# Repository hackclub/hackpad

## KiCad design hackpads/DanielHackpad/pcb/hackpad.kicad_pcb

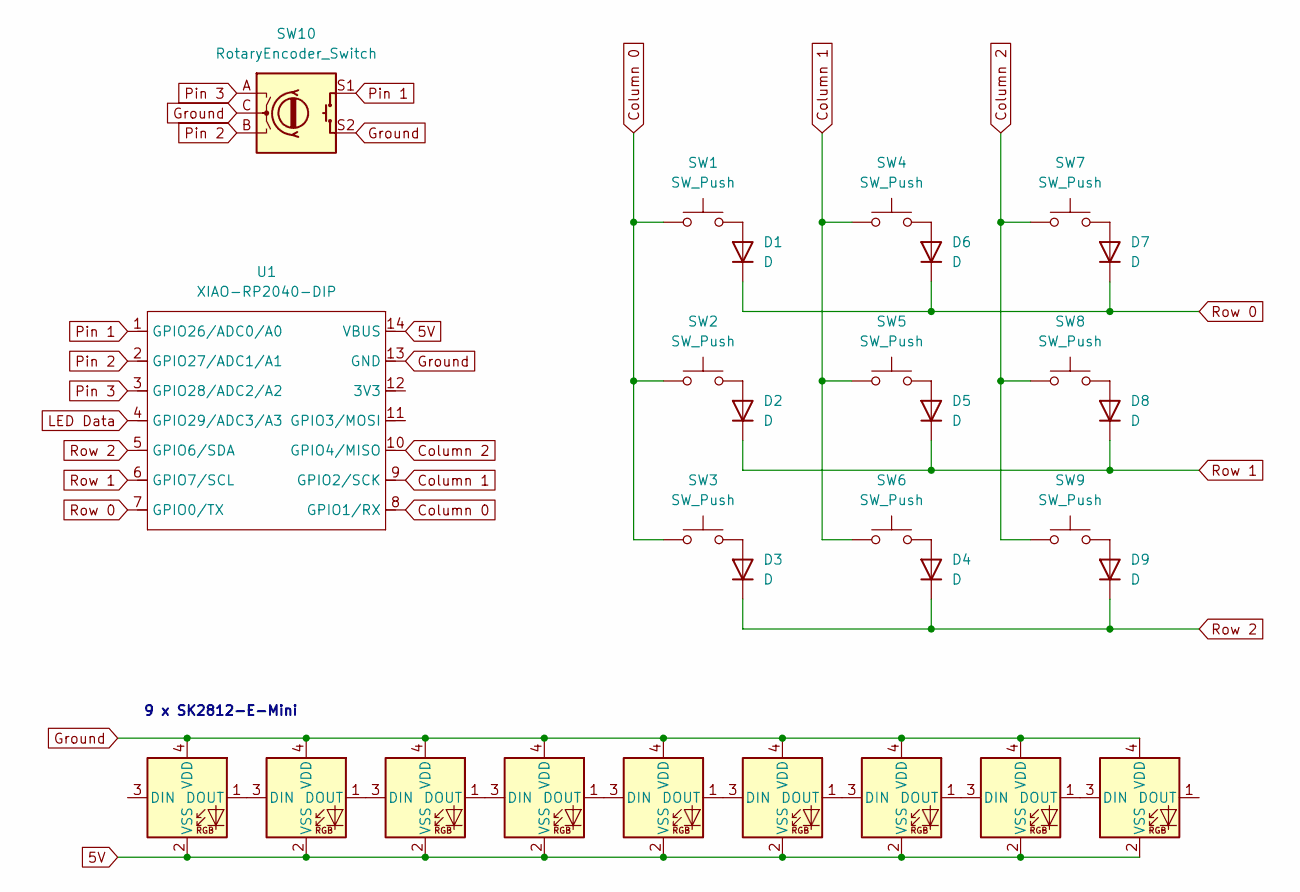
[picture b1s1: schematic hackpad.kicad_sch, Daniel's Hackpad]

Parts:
D1, D2, D3, D4, D5, D6, D7, D8, D9: D; D_DO-35_SOD27_P7.62mm_Horizontal
D10, D11, D12, D13, D14, D15, D16, D17, D19: SK6812MINI; SK6812MINI-E
SW1, SW2, SW3, SW4, SW5, SW6, SW7, SW8, SW9: SW_Push; SW_Cherry_MX_1.00u_PCB
SW10: RotaryEncoder_Switch; RotaryEncoder_Alps_EC11E-Switch_Vertical_H20mm_CircularMoun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
U1: XIAO-RP2040-DIP

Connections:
5V: D10.2 (VSS), D11.2 (VSS), D12.2 (VSS), D13.2 (VSS), D14.2 (VSS), D15.2 (VSS), D16.2 (VSS), D17.2 (VSS), D19.2 (VSS), U1.14 (VBUS)
Column 0: SW1.1, SW2.1, SW3.1, U1.8 (GPIO1/RX)
Column 1: SW4.1, SW5.1, SW6.1, U1.9 (GPIO2/SCK)
Column 2: SW7.1, SW8.1, SW9.1, U1.10 (GPIO4/MISO)
Ground: D10.4 (VDD), D11.4 (VDD), D12.4 (VDD), D13.4 (VDD), D14.4 (VDD), D15.4 (VDD), D16.4 (VDD), D17.4 (VDD), D19.4 (VDD), SW10.C, SW10.S2, U1.13 (GND)
LED Data: U1.4 (GPIO29/ADC3/A3)
unnamed: D1.2 (A), SW1.2
unnamed: D2.2 (A), SW2.2
unnamed: D3.2 (A), SW3.2
unnamed: D4.2 (A), SW6.2
unnamed: D5.2 (A), SW5.2
unnamed: D6.2 (A), SW4.2
unnamed: D7.2 (A), SW7.2
unnamed: D8.2 (A), SW8.2
unnamed: D9.2 (A), SW9.2
unnamed: D10.3 (DIN), D19.1 (DOUT)
unnamed: D10.1 (DOUT), D11.3 (DIN)
unnamed: D11.1 (DOUT), D12.3 (DIN)
unnamed: D12.1 (DOUT), D13.3 (DIN)
unnamed: D13.1 (DOUT), D14.3 (DIN)
unnamed: D14.1 (DOUT), D15.3 (DIN)
unnamed: D15.1 (DOUT), D16.3 (DIN)
unnamed: D16.1 (DOUT), D17.3 (DIN)
Pin 1: SW10.S1, U1.1 (GPIO26/ADC0/A0)
Pin 2: SW10.B, U1.2 (GPIO27/ADC1/A1)
Pin 3: SW10.A, U1.3 (GPIO28/ADC2/A2)
Row 0: D1.1 (K), D6.1 (K), D7.1 (K), U1.7 (GPIO0/TX)
Row 1: D2.1 (K), D5.1 (K), D8.1 (K), U1.6 (GPIO7/SCL)
Row 2: D3.1 (K), D4.1 (K), D9.1 (K), U1.5 (GPIO6/SDA)

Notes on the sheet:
9 x SK2812-E-Mini

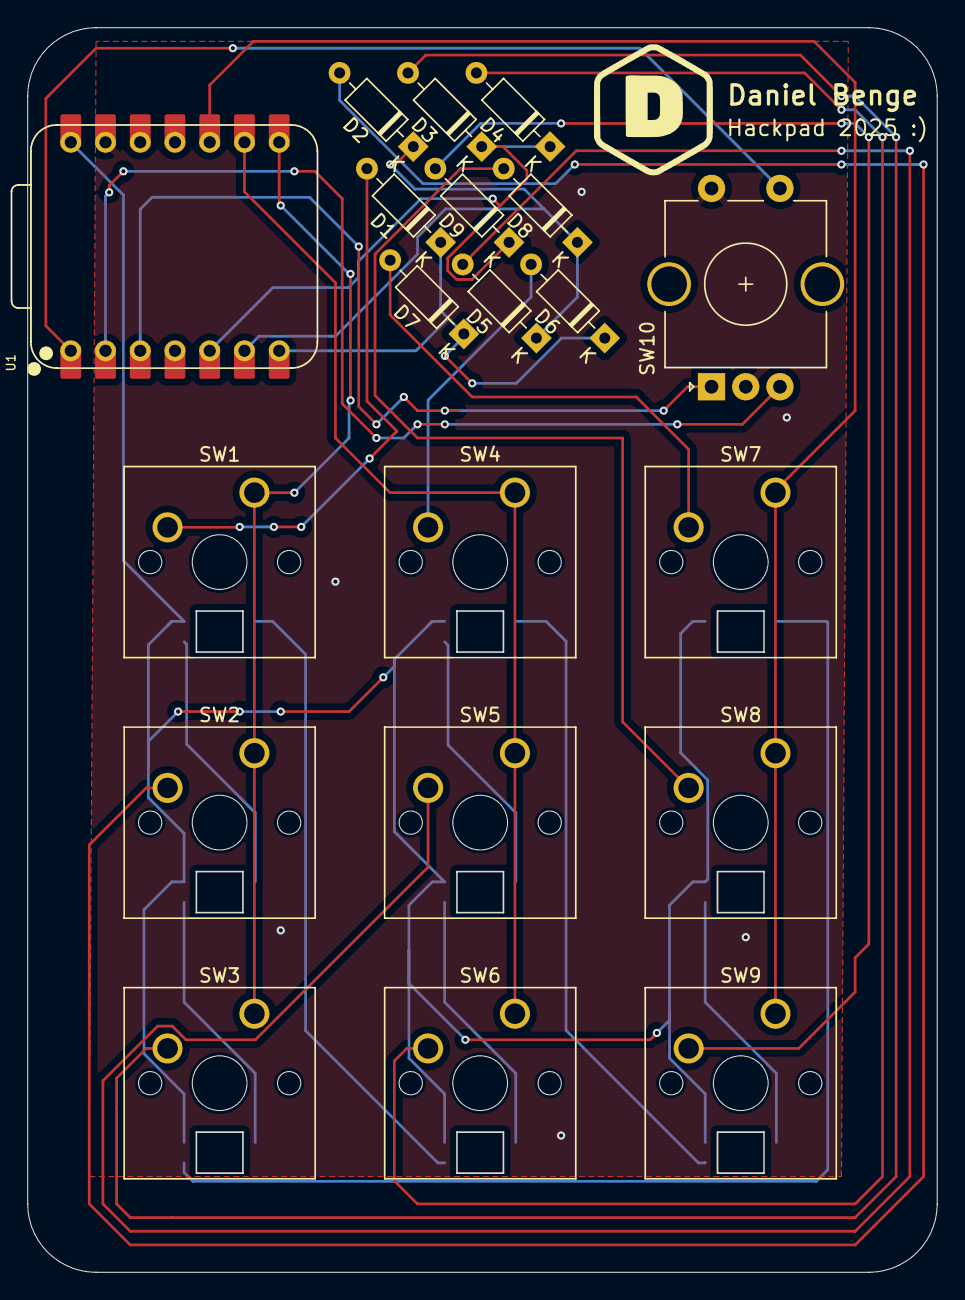
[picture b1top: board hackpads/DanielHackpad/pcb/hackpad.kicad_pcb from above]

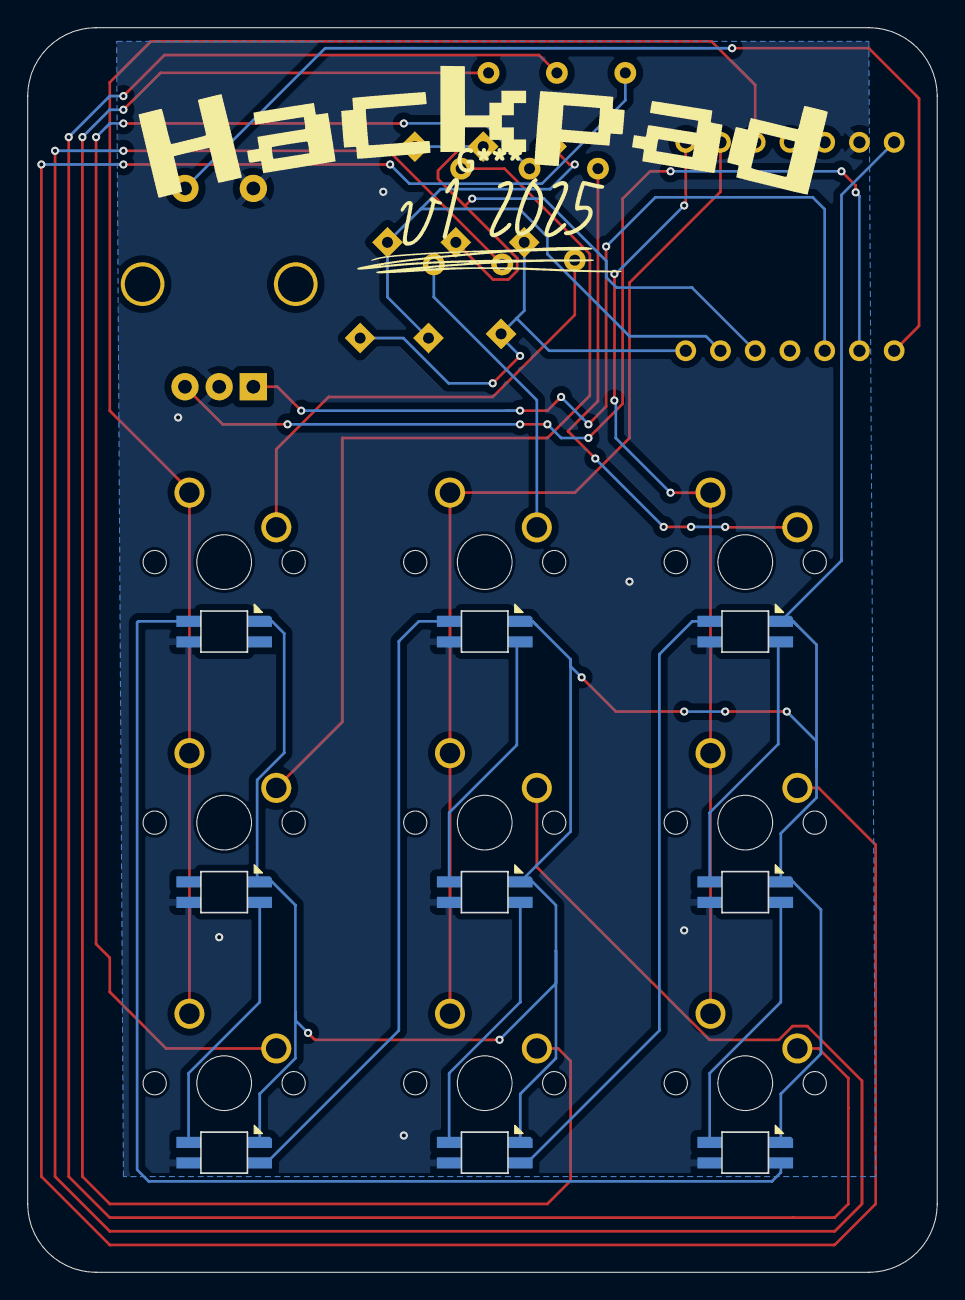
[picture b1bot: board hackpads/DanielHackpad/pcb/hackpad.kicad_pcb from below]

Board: 2 copper layers, 66.5 x 91.0 mm, 29 parts (9 on the bottom side), 28 nets.

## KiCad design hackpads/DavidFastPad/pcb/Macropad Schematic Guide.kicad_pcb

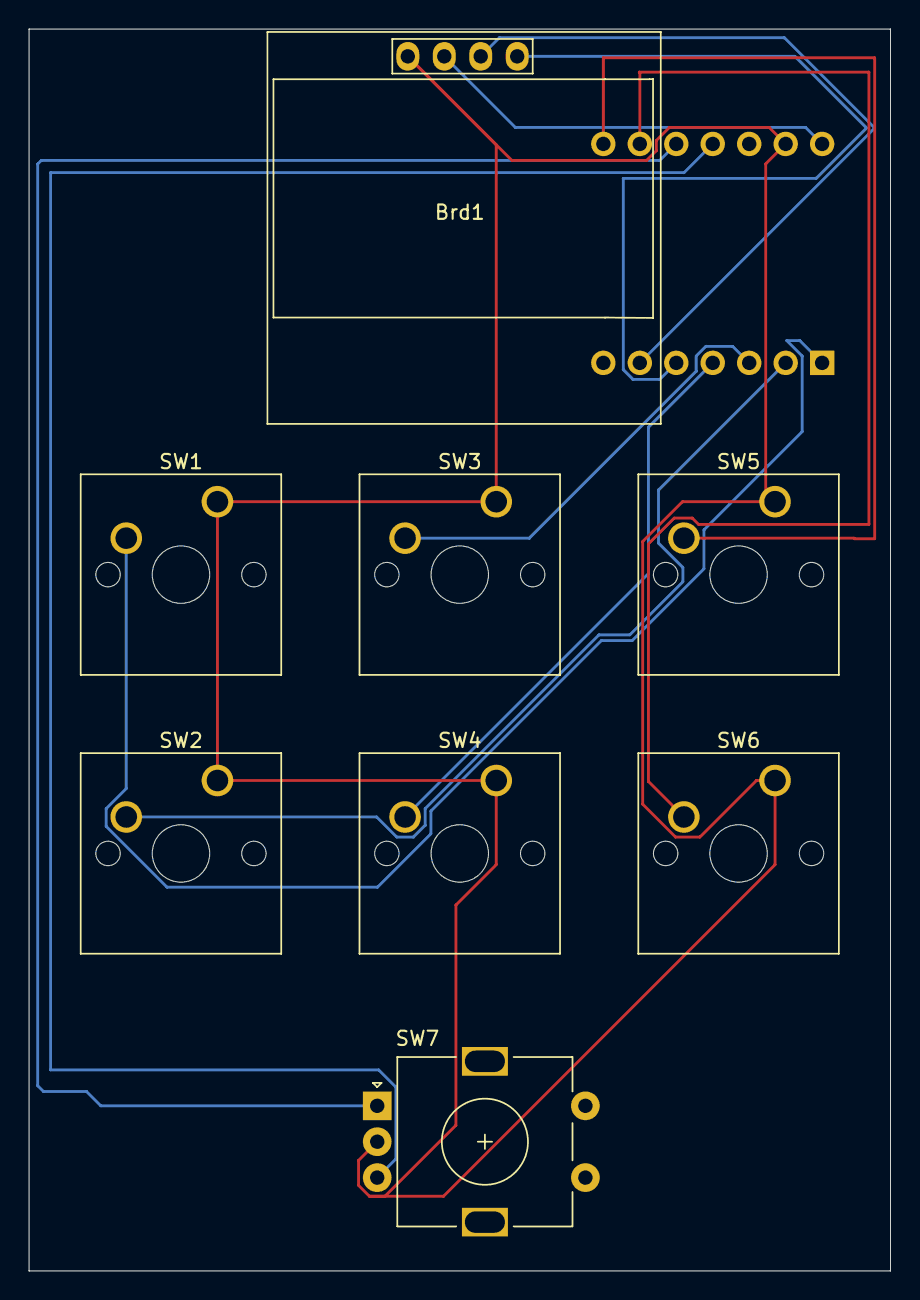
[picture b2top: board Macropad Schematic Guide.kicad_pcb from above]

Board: 2 copper layers, 60.0 x 86.5 mm, 9 parts (1 on the bottom side), 12 nets.

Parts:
Brd1: SSD1306; 128x64OLED
SW1, SW2, SW3, SW4, SW5, SW6: SW_Push; SW_Cherry_MX_1.00u_PCB
SW7: RotaryEncoder; RotaryEncoder_Alps_EC11E-Switch_Vertical_H20mm
U1: Seeed Studio XIAO SAMD21; XIAO-Generic-Thruhole-14P-2.54-21X17.8MM

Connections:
1: SW1.2, U1.1 (PA02_A0_D0)
2: SW2.2, U1.2 (PA4_A1_D1)
3: SW3.2, U1.3 (PA10_A2_D2)
4: SW4.2, U1.4 (PA11_A3_D3)
5: SW5.2, U1.8 (PB09_A7_D7_RX)
6: SW6.2, U1.9 (PA7_A8_D8_SCK)
A: SW7.A, U1.10 (PA5_A9_D9_MISO)
B: SW7.B, U1.11 (PA6_A10_D10_MOSI)
GND: Brd1.1 (GND), SW1.1, SW2.1, SW3.1, SW4.1, SW5.1, SW6.1, SW7.C, U1.13 (GND)
SCL: Brd1.3 (SCL), U1.6 (PA9_A5_D5_SCL)
SDA: Brd1.4 (SDA), U1.5 (PA8_A4_D4_SDA)
VCC: Brd1.2 (VCC), U1.14 (5V)

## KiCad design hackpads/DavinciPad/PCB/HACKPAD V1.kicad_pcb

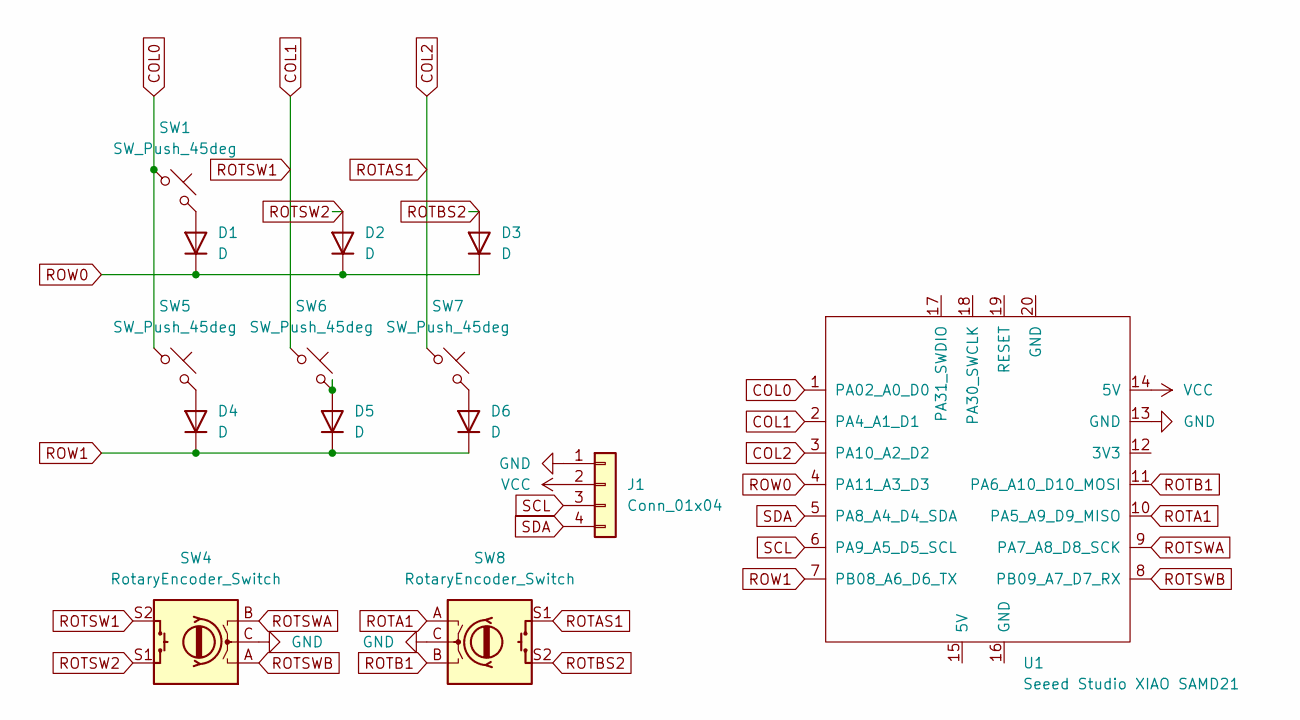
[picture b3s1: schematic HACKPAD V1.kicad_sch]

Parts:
D1, D2, D3, D4, D5, D6: D; D_DO-35_SOD27_P7.62mm_Horizontal
J1: Conn_01x04; SSD1306-0.91-OLED-4pin-128x32
SW1, SW5, SW6, SW7: SW_Push_45deg; SW_Cherry_MX_1.00u_PCB
SW4, SW8: RotaryEncoder_Switch; RotaryEncoder_Alps_EC11E-Switch_Vertical_H20mm
U1: Seeed Studio XIAO SAMD21; XIAO-Generic-Thruhole-14P-2.54-21X17.8MM

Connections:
COL0: SW1.1, SW5.1, U1.1 (PA02_A0_D0)
COL1: SW4.S2, SW6.1, U1.2 (PA4_A1_D1)
COL2: SW7.1, SW8.S1, U1.3 (PA10_A2_D2)
GND: J1.1, SW4.C, SW8.C, U1.13 (GND)
unnamed: D1.2 (A), SW1.2
unnamed: D4.2 (A), SW5.2
unnamed: D5.2 (A), SW6.2
unnamed: D6.2 (A), SW7.2
ROTA1: SW8.A, U1.10 (PA5_A9_D9_MISO)
ROTB1: SW8.B, U1.11 (PA6_A10_D10_MOSI)
ROTBS2: D3.2 (A), SW8.S2
ROTSW2: D2.2 (A), SW4.S1
ROTSWA: SW4.B, U1.9 (PA7_A8_D8_SCK)
ROTSWB: SW4.A, U1.8 (PB09_A7_D7_RX)
ROW0: D1.1 (K), D2.1 (K), D3.1 (K), U1.4 (PA11_A3_D3)
ROW1: D4.1 (K), D5.1 (K), D6.1 (K), U1.7 (PB08_A6_D6_TX)
SCL: J1.3, U1.6 (PA9_A5_D5_SCL)
SDA: J1.4, U1.5 (PA8_A4_D4_SDA)
VCC: J1.2, U1.14 (5V)

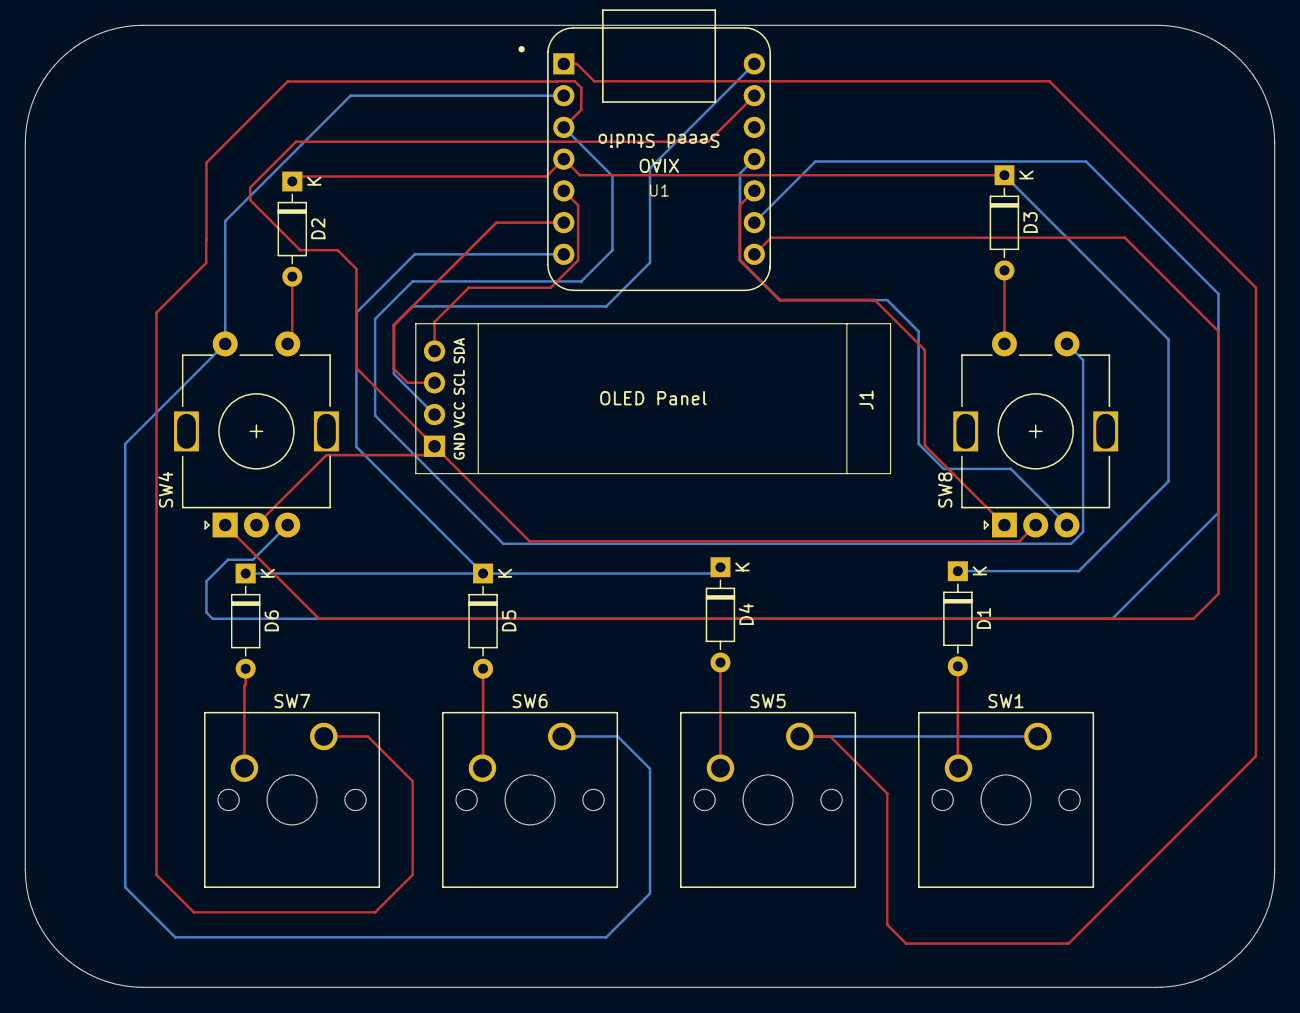
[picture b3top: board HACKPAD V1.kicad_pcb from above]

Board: 2 copper layers, 100.0 x 77.0 mm, 14 parts (0 on the bottom side), 19 nets.

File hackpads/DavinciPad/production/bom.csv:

Designator,Footprint,Quantity,Value,LCSC Part #
"D1, D2, D3, D4, D5, D6",D_DO-35_SOD27_P7.62mm_Horizontal,6,D,
J1,SSD1306-0.91-OLED-4pin-128x32,1,Conn_01x04,
"SW1, SW5, SW6, SW7",SW_Cherry_MX_1.00u_PCB,4,SW_Push_45deg,
"SW4, SW8",RotaryEncoder_Alps_EC11E-Switch_Vertical_H20mm,2,RotaryEncoder_Switch,
U1,XIAO-Generic-Thruhole-14P-2.54-21X17.8MM,1,Seeed Studio XIAO SAMD21,

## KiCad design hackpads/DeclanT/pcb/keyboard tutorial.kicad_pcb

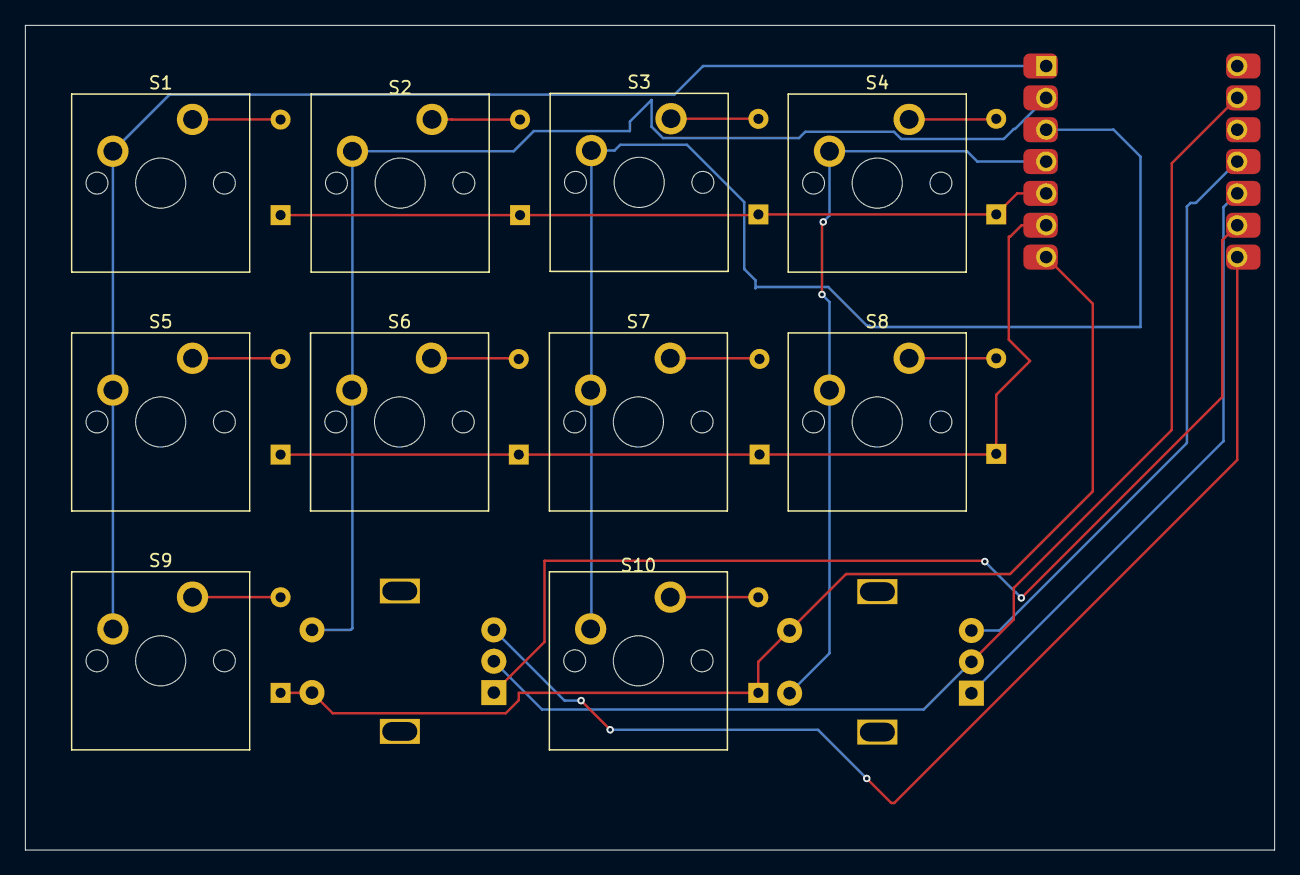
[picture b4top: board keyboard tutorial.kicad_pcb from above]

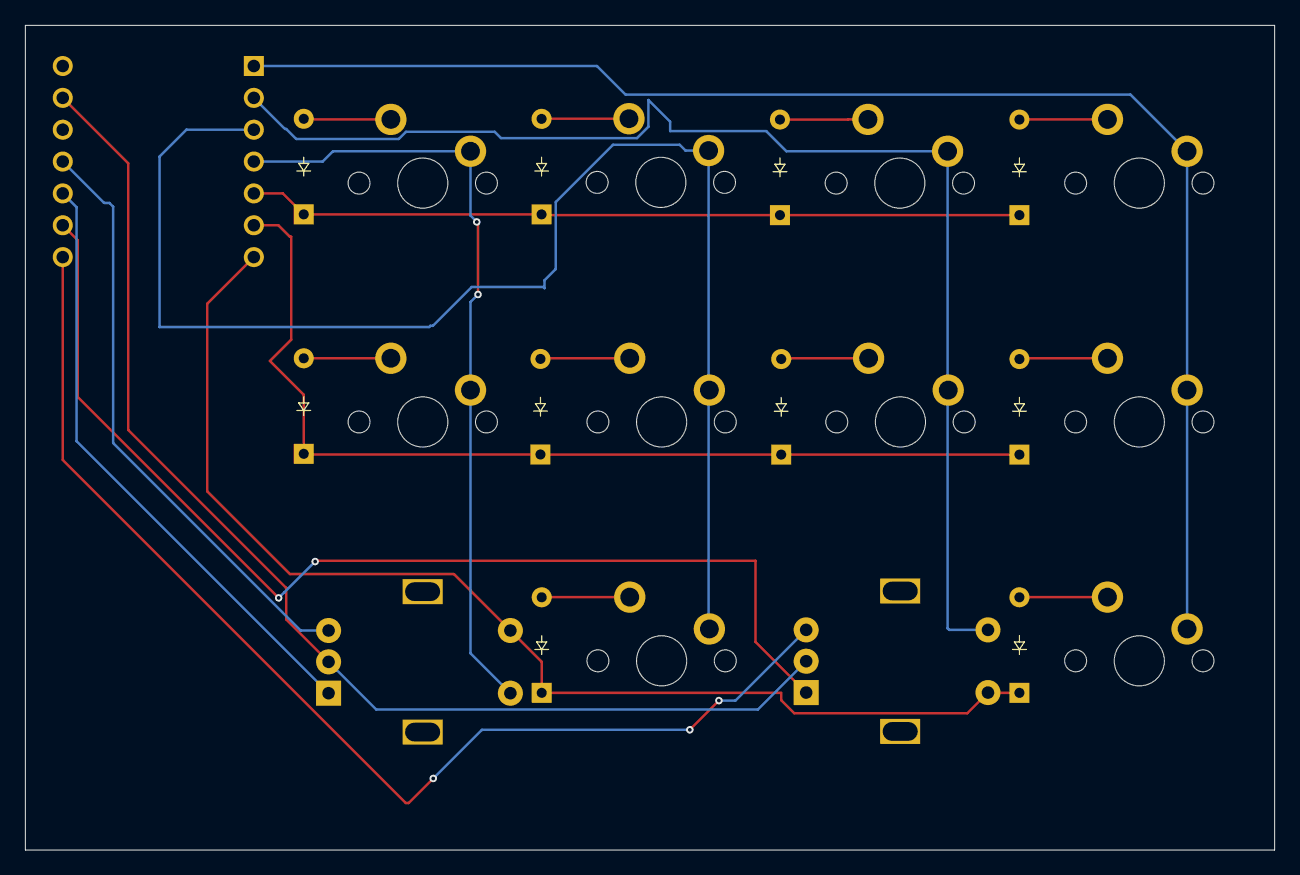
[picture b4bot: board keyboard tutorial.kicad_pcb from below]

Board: 2 copper layers, 99.6 x 65.8 mm, 23 parts (10 on the bottom side), 22 nets.

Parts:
D1, D2, D3, D4, D5, D6, D7, D9, D10, D11: Diode; Diode_DO-35
S1, S2, S3, S4, S5, S6, S7, S8, S9, S10: Keyswitch; MX_PCB_1.00u
SW1, SW2: RotaryEncoder_Switch; Encoder_EC11_MX
U2: MOUDLE-SEEEDUINO-XIAO; Seeed_XIAO_RP2040

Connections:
GND: SW1.C, SW2.C, U2.13 (GND)
unnamed: D1.2 (A), S1.2
unnamed: D2.2 (A), S3.2
unnamed: D3.2 (A), S2.2
unnamed: D4.2 (A), S5.2
unnamed: D5.2 (A), S6.2
unnamed: D6.2 (A), S7.2
unnamed: D7.2 (A), S9.2
unnamed: D9.2 (A), S10.2
unnamed: D10.2 (A), S4.2
unnamed: D11.2 (A), S8.2
Rotary 1: SW1.B, U2.11 (PA6_A10_D10_MOSI)
Rotary 2: SW1.A, U2.10 (PA5_A9_D9_MISO)
Rotary 3: SW2.A, U2.9 (PA7_A8_D8_SCK)
Rotary 4: SW2.B, U2.8 (PB09_A7_D7_RX)
column 0: S1.1, S5.1, S9.1, U2.1 (PA02_A0_D0)
column 1: S2.1, S6.1, SW2.S1, U2.2 (PA4_A1_D1)
column 2: S3.1, S7.1, S10.1, U2.3 (PA10_A2_D2)
column 3: S4.1, S8.1, SW1.S2, U2.4 (PA11_A3_D3)
row 0: D1.1 (K), D2.1 (K), D3.1 (K), D10.1 (K), U2.5 (PA8_A4_D4_SDA)
row 1: D4.1 (K), D5.1 (K), D6.1 (K), D11.1 (K), U2.6 (PA9_A5_D5_SCL)
row 2: D7.1 (K), D9.1 (K), SW1.S1, SW2.S2, U2.7 (PB08_A6_D6_TX)

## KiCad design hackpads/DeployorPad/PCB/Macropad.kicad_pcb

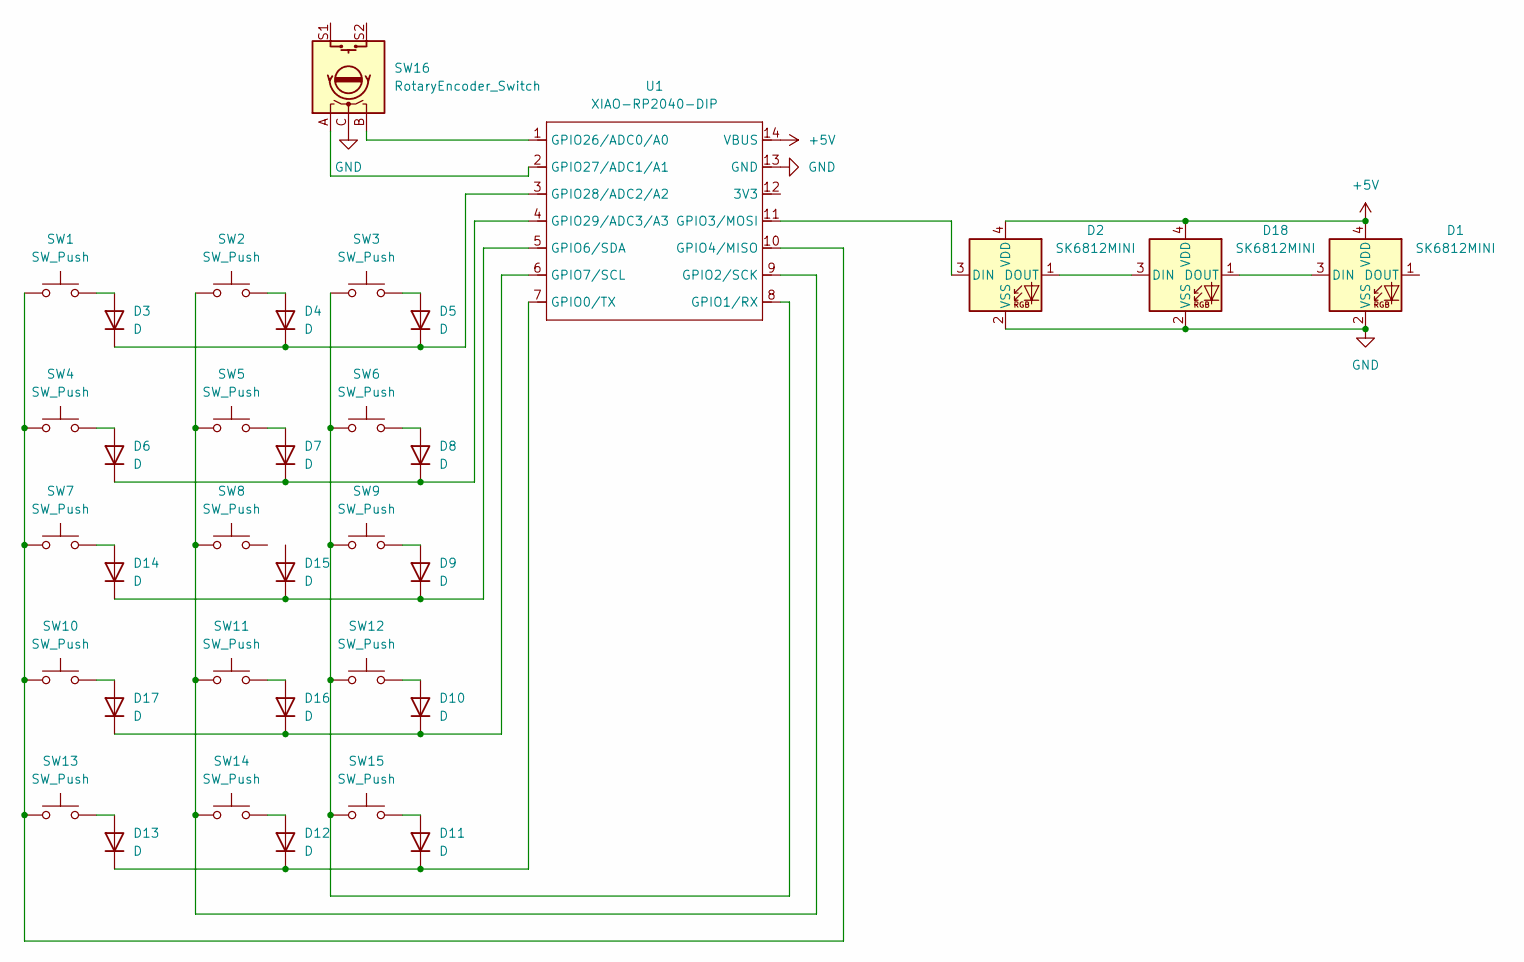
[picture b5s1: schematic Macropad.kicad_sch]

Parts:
D1, D2, D18: SK6812MINI; LED_SK6812MINI_PLCC4_3.5x3.5mm_P1.75mm
D3, D4, D5, D6, D7, D8, D9, D10, D11, D12, D13, D14, D15, D16, D17: D; D_DO-35_SOD27_P7.62mm_Horizontal
SW1, SW2, SW3, SW4, SW5, SW6, SW7, SW8, SW9, SW10, SW11, SW12, SW13, SW14, SW15: SW_Push; SW_Cherry_MX_1.00u_PCB
SW16: RotaryEncoder_Switch; RotaryEncoder_Alps_EC11E-Switch_Vertical_H20mm_CircularMoun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
U1: XIAO-RP2040-DIP

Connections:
+5V: D1.4 (VDD), D2.4 (VDD), D18.4 (VDD), U1.14 (VBUS)
GND: D1.2 (VSS), D2.2 (VSS), D18.2 (VSS), SW16.C, U1.13 (GND)
unnamed: D1.3 (DIN), D18.1 (DOUT)
unnamed: D2.3 (DIN), U1.11 (GPIO3/MOSI)
unnamed: D3.2 (A), SW1.2
unnamed: D3.1 (K), D4.1 (K), D5.1 (K), U1.3 (GPIO28/ADC2/A2)
unnamed: D4.2 (A), SW2.2
unnamed: D5.2 (A), SW3.2
unnamed: D6.2 (A), SW4.2
unnamed: D6.1 (K), D7.1 (K), D8.1 (K), U1.4 (GPIO29/ADC3/A3)
unnamed: D7.2 (A), SW5.2
unnamed: D8.2 (A), SW6.2
unnamed: D9.2 (A), SW9.2
unnamed: D10.2 (A), SW12.2
unnamed: D10.1 (K), D16.1 (K), D17.1 (K), U1.6 (GPIO7/SCL)
unnamed: D11.2 (A), SW15.2
unnamed: D11.1 (K), D12.1 (K), D13.1 (K), U1.7 (GPIO0/TX)
unnamed: D12.2 (A), SW14.2
unnamed: D13.2 (A), SW13.2
unnamed: D14.2 (A), SW7.2
unnamed: D9.1 (K), D14.1 (K), D15.1 (K), U1.5 (GPIO6/SDA)
unnamed: D16.2 (A), SW11.2
unnamed: D17.2 (A), SW10.2
unnamed: D2.1 (DOUT), D18.3 (DIN)
unnamed: SW3.1, SW6.1, SW9.1, SW12.1, SW15.1, U1.8 (GPIO1/RX)
unnamed: SW2.1, SW5.1, SW8.1, SW11.1, SW14.1, U1.9 (GPIO2/SCK)
unnamed: SW1.1, SW4.1, SW7.1, SW10.1, SW13.1, U1.10 (GPIO4/MISO)
unnamed: SW16.B, U1.1 (GPIO26/ADC0/A0)
unnamed: SW16.A, U1.2 (GPIO27/ADC1/A1)

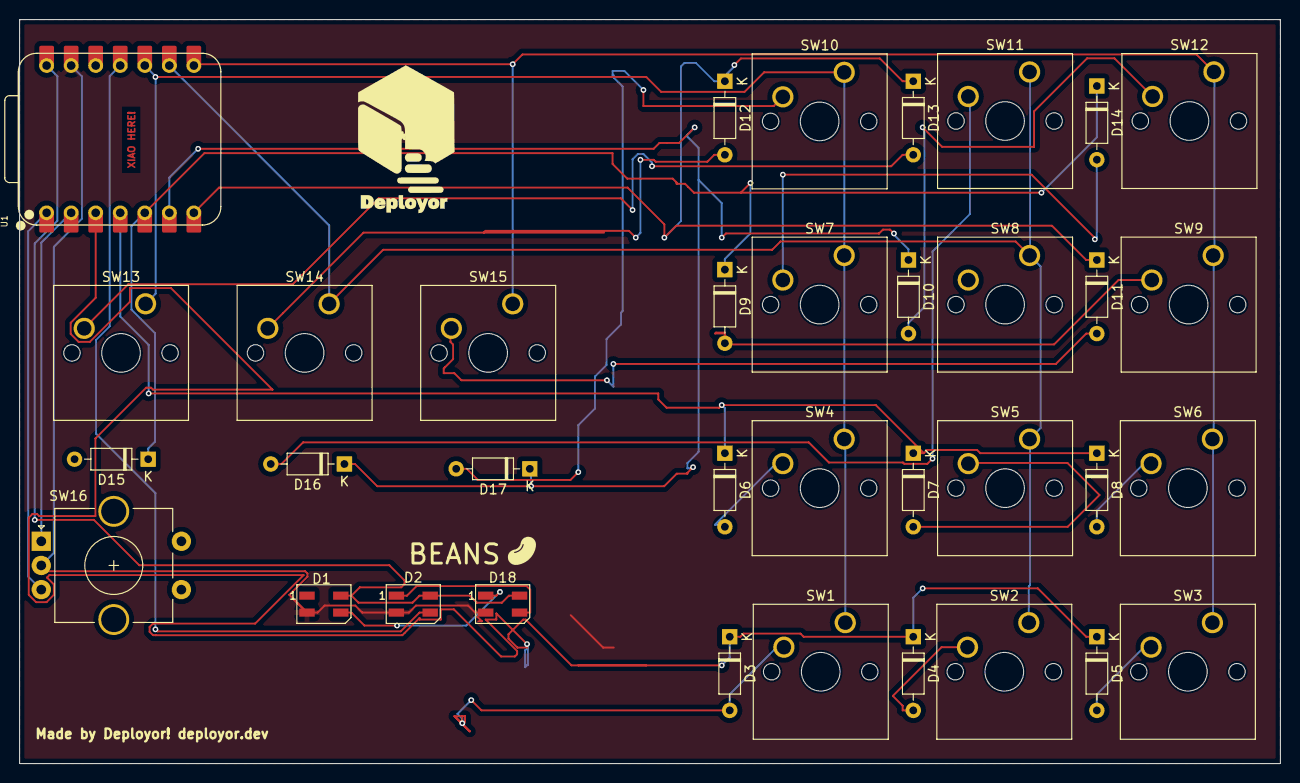
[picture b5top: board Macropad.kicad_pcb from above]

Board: 2 copper layers, 130.5 x 77.0 mm, 35 parts (0 on the bottom side), 29 nets.

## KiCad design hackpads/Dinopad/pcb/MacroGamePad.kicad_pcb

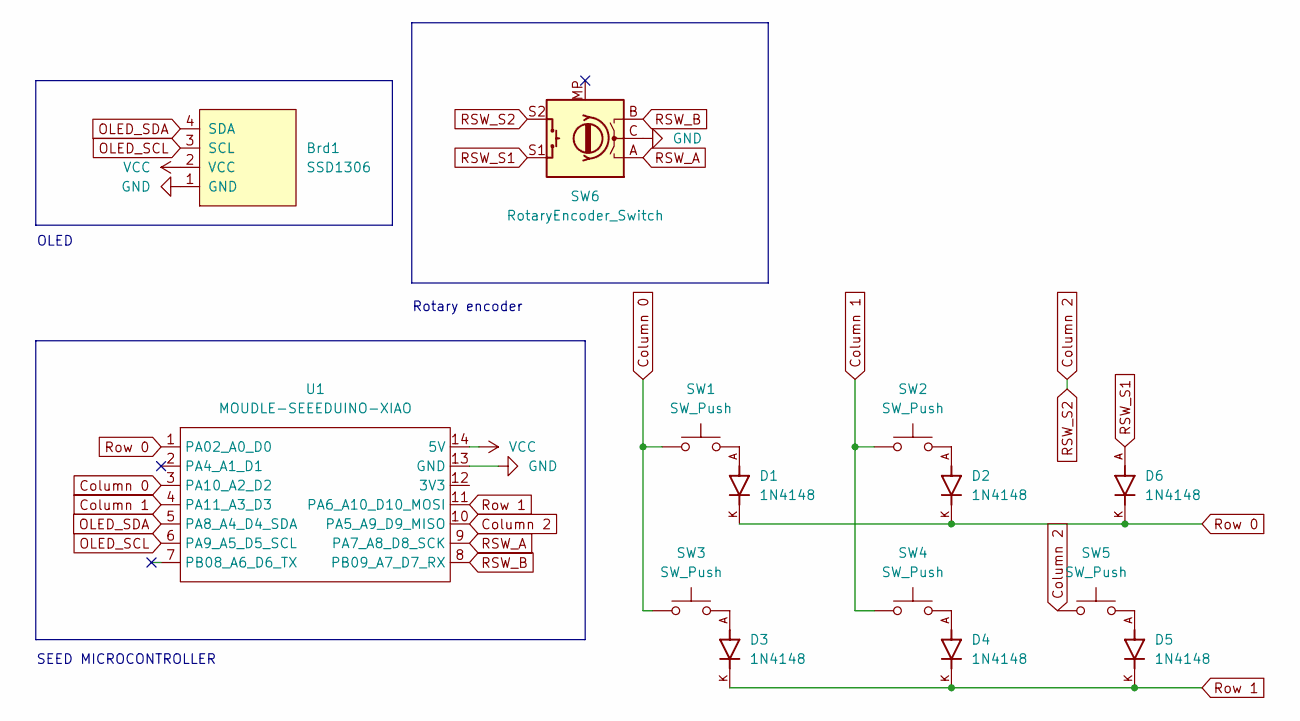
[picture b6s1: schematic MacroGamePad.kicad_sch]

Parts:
Brd1: SSD1306; SSD1306 128x64 OLED
D1, D2, D3, D4, D5, D6: 1N4148; 1N4148 Diode; PARTREV 5
SW1, SW2, SW3, SW4, SW5: SW_Push; SW_Cherry_MX_1.00u_PCB
SW6: RotaryEncoder_Switch; RotaryEncoder_Alps_EC11E-Switch_Vertical_H20mm
U1: MOUDLE-SEEEDUINO-XIAO; XIAO-Generic-Hybrid-14P-2.54-21X17.8MM

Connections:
Column 0: SW1.1, SW3.1, U1.3 (PA10_A2_D2)
Column 1: SW2.1, SW4.1, U1.4 (PA11_A3_D3)
Column 2: SW5.1, SW6.S2, U1.10 (PA5_A9_D9_MISO)
GND: Brd1.1 (GND), SW6.C, U1.13 (GND)
unnamed: D1.A, SW1.2
unnamed: D2.A, SW2.2
unnamed: D3.A, SW3.2
unnamed: D4.A, SW4.2
unnamed: D5.A, SW5.2
OLED_SCL: Brd1.3 (SCL), U1.6 (PA9_A5_D5_SCL)
OLED_SDA: Brd1.4 (SDA), U1.5 (PA8_A4_D4_SDA)
RSW_A: SW6.A, U1.9 (PA7_A8_D8_SCK)
RSW_B: SW6.B, U1.8 (PB09_A7_D7_RX)
RSW_S1: D6.A, SW6.S1
Row 0: D1.K, D2.K, D6.K, U1.1 (PA02_A0_D0)
Row 1: D3.K, D4.K, D5.K, U1.11 (PA6_A10_D10_MOSI)
VCC: Brd1.2 (VCC), U1.14 (5V)

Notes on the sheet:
SEED MICROCONTROLLER
Rotary encoder
OLED

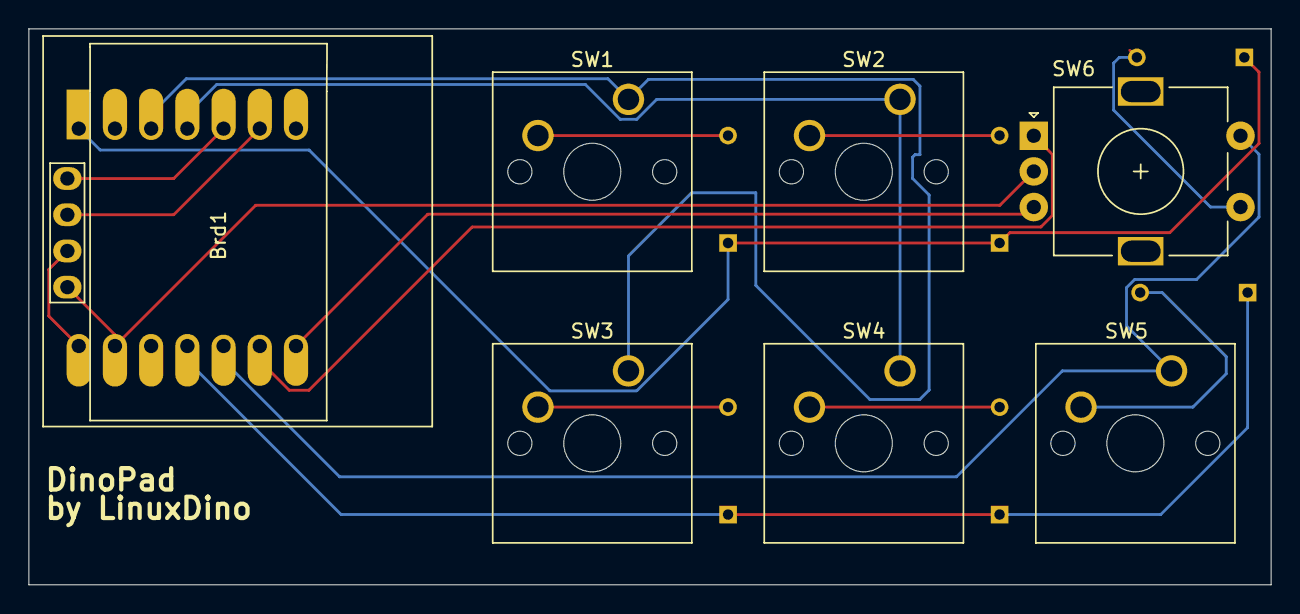
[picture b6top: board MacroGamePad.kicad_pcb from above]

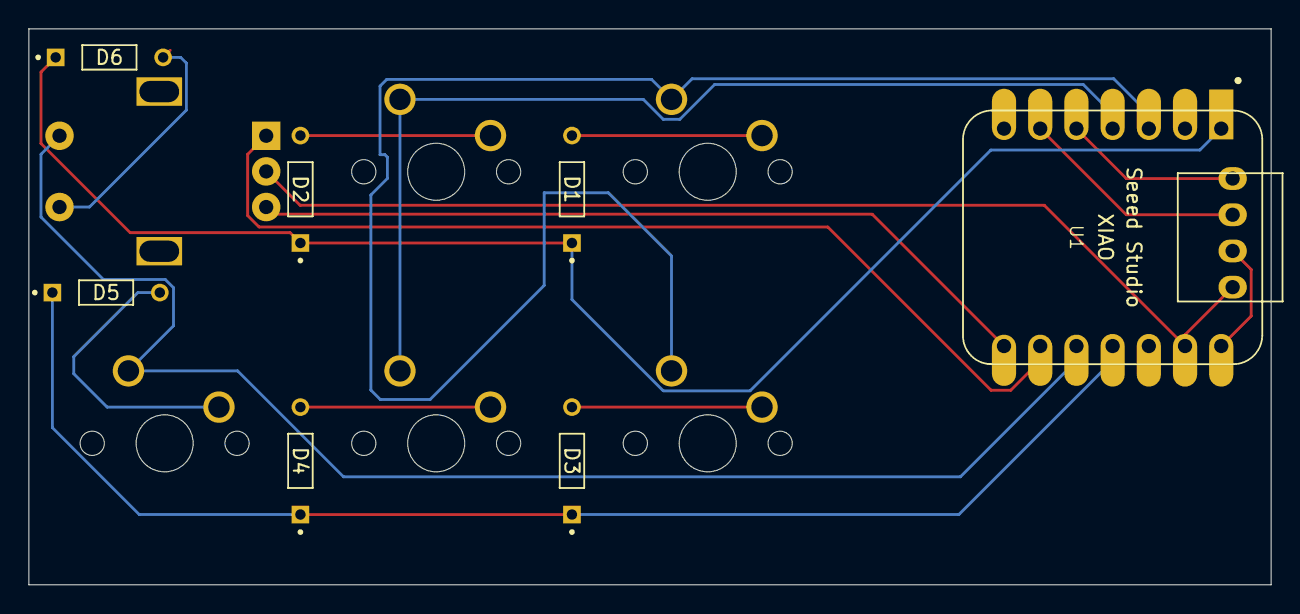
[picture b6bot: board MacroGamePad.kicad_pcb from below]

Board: 2 copper layers, 87.2 x 39.0 mm, 14 parts (7 on the bottom side), 17 nets.

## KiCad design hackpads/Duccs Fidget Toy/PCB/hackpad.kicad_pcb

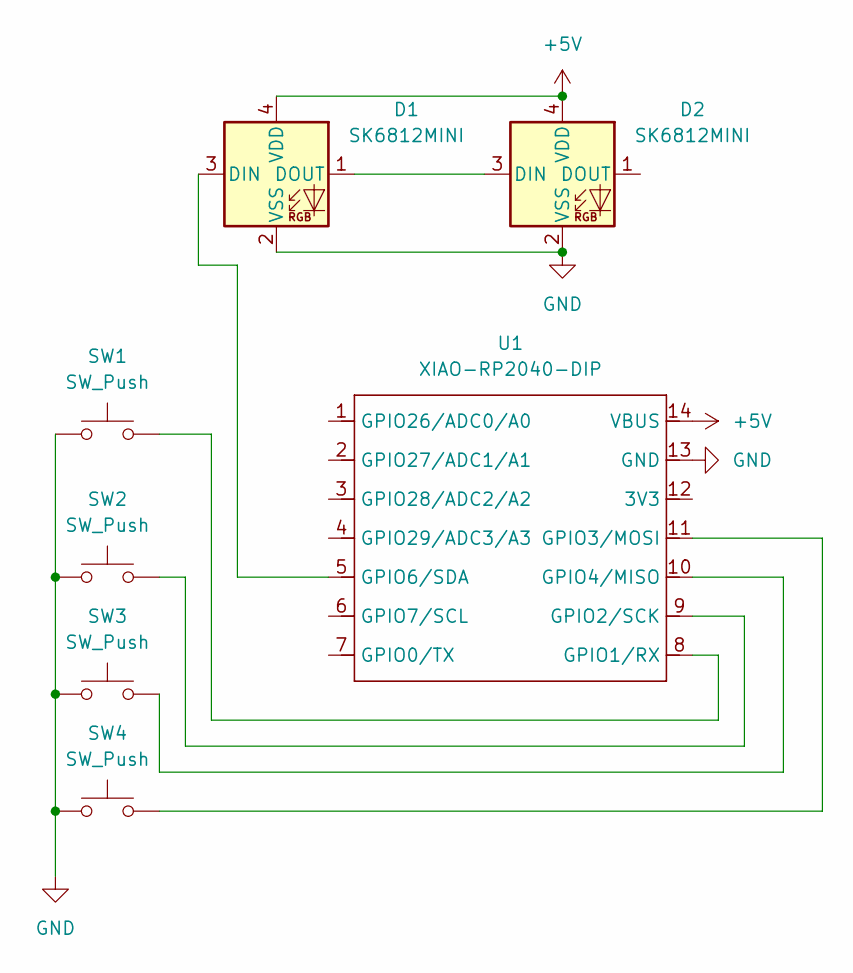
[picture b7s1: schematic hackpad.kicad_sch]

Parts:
D1, D2: SK6812MINI; LED_SK6812MINI_PLCC4_3.5x3.5mm_P1.75mm
SW1, SW2, SW3, SW4: SW_Push; SW_Cherry_MX_1.00u_PCB
U1: XIAO-RP2040-DIP

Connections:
+5V: D1.4 (VDD), D2.4 (VDD), U1.14 (VBUS)
GND: D1.2 (VSS), D2.2 (VSS), SW1.2, SW2.2, SW3.2, SW4.2, U1.13 (GND)
unnamed: D1.3 (DIN), U1.5 (GPIO6/SDA)
unnamed: D1.1 (DOUT), D2.3 (DIN)
unnamed: SW1.1, U1.8 (GPIO1/RX)
unnamed: SW2.1, U1.9 (GPIO2/SCK)
unnamed: SW4.1, U1.11 (GPIO3/MOSI)
unnamed: SW3.1, U1.10 (GPIO4/MISO)

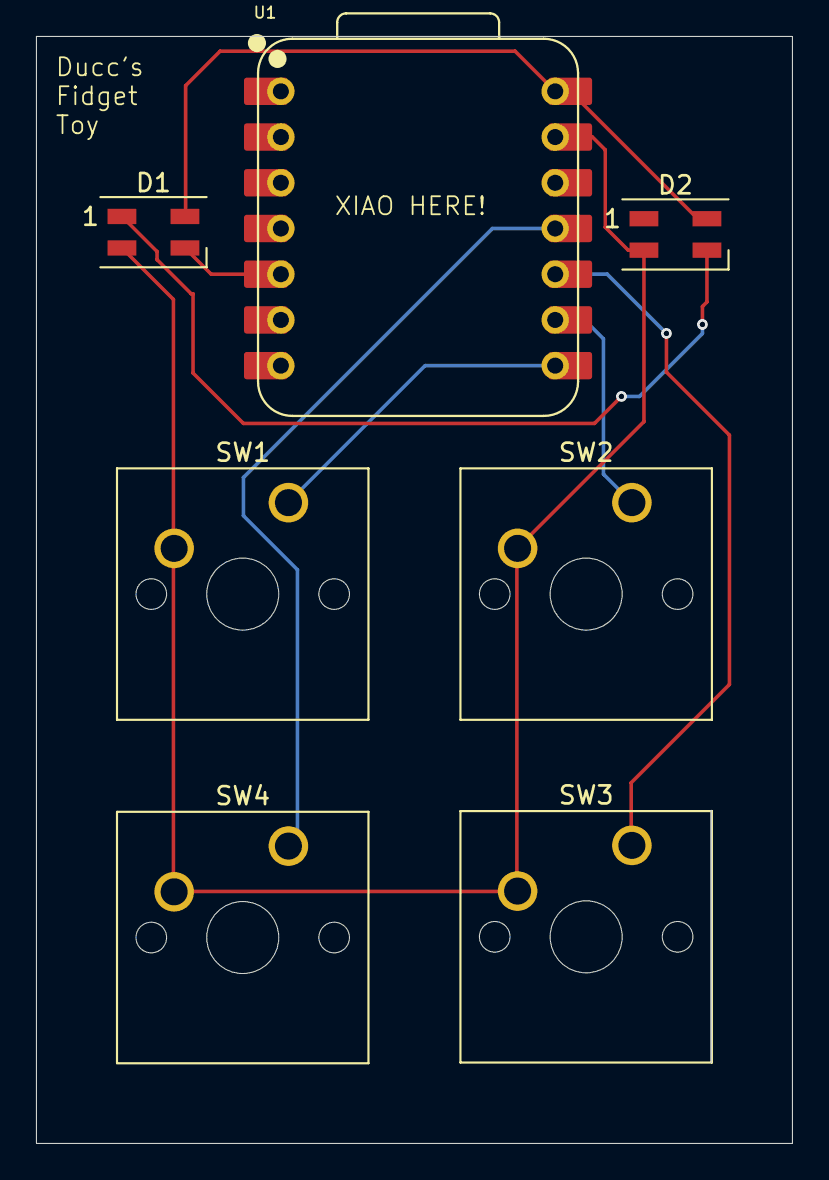
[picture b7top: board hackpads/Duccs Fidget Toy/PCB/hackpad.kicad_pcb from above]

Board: 2 copper layers, 42.0 x 61.5 mm, 7 parts (0 on the bottom side), 8 nets.
